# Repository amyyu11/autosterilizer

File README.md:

# autosterilizer
Automatic Ethanol Sterilizer Project repository. Done in collaboration with 5 other people from UCLA BMES.

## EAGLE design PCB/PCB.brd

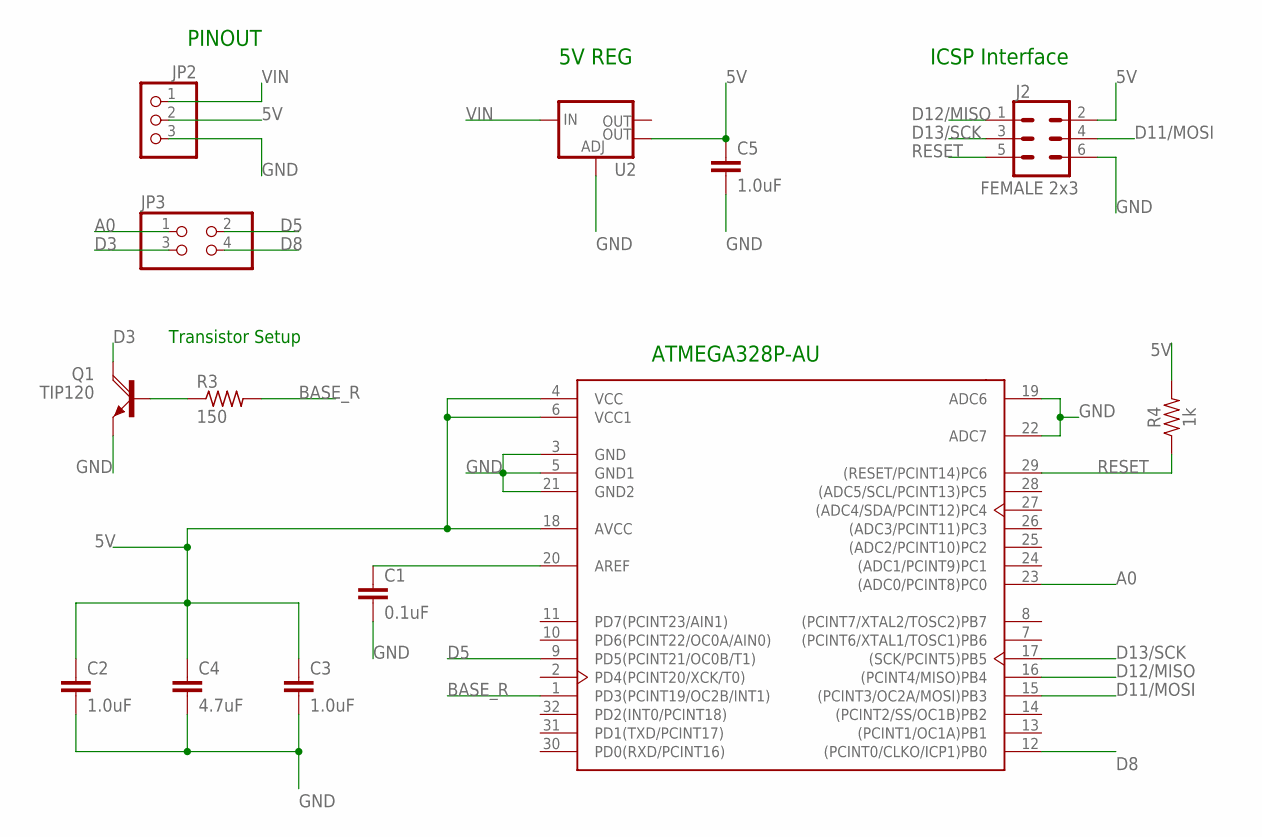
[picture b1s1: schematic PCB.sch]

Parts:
C1: 0.1uF; 0603
C2, C3, C5: 1.0uF; 0603
C4: 4.7uF; 1206
J2: FEMALE 2x3; 2X3
JP2: PINHEAD_PINHD-1X3; PINHEAD_1X03
JP3: PINHD-2X2; 2X02
Q1: TIP120; TO220AH
R3: 150; R0805
R4: 1k; 0603
U1: ATMEGA328P-AU; TQFP-32
U2: V_REG_LM1117SOT223; SOT223

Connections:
5V: C2.1, C3.1, C4.1, C5.1, J2.2, JP2.2, R4.2, U1.4 (VCC), U1.6 (VCC1), U1.18 (AVCC), U2.4 (OUT)
A0: JP3.1, U1.23 ((ADC0/PCINT8)PC0)
BASE_R: R3.2, U1.1 (PD3(PCINT19/OC2B/INT1))
D3: JP3.3, Q1.C
D5: JP3.2, U1.9 (PD5(PCINT21/OC0B/T1))
D8: JP3.4, U1.12 ((PCINT0/CLKO/ICP1)PB0)
D11/MOSI: J2.4, U1.15 ((PCINT3/OC2A/MOSI)PB3)
D12/MISO: J2.1, U1.16 ((PCINT4/MISO)PB4)
D13/SCK: J2.3, U1.17 ((SCK/PCINT5)PB5)
GND: C1.2, C2.2, C3.2, C4.2, C5.2, J2.6, JP2.3, Q1.E, U1.3 (GND), U1.5 (GND1), U1.19 (ADC6), U1.21 (GND2), U1.22 (ADC7), U2.1 (ADJ)
unnamed: Q1.B, R3.1
unnamed: C1.1, U1.20 (AREF)
RESET: J2.5, R4.1, U1.29 ((RESET/PCINT14)PC6)
VIN: JP2.1, U2.3 (IN)

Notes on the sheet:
ICSP Interface
5V REG
PINOUT
ATMEGA328P-AU
Transistor Setup

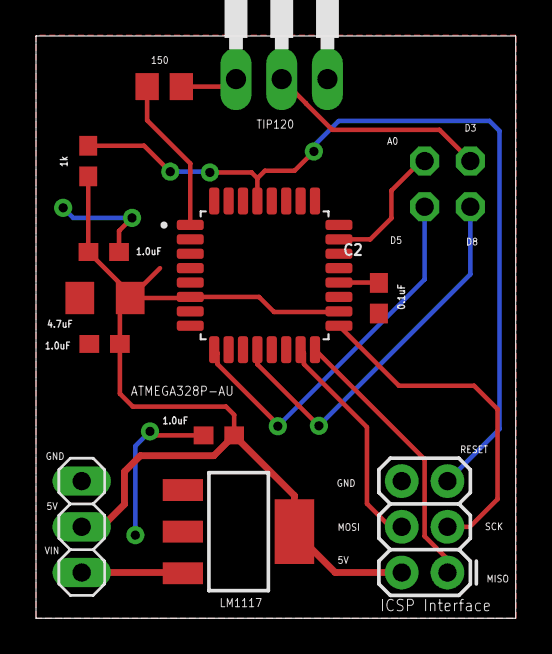
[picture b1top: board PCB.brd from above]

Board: 2 copper layers, 26.6 x 32.3 mm, 13 parts (1 on the bottom side), 14 nets.

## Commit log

2020-08-27 Added project files.
2020-08-27 hello
2020-08-27 removed some files.
2020-08-27 Added more project files.
2020-08-27 Reorganized directory structure
2020-08-27 Restructured directories.
2020-08-27 Cleaned up repo.

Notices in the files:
parts and their libraries:
SparkFun-Capacitors: Licensing: Creative Commons ShareAlike 4.0 International - https://creativecommons.org/licenses/by-sa/4.0
